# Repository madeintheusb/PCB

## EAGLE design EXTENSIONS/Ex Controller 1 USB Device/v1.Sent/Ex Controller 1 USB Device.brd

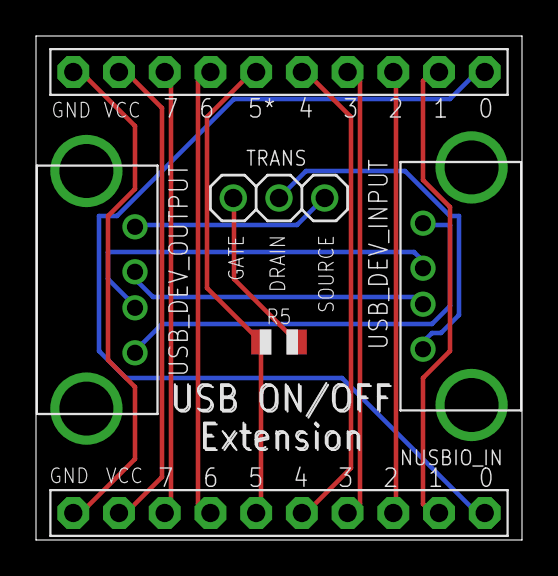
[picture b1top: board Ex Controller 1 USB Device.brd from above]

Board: 2 copper layers, 27.0 x 28.0 mm, 6 parts (0 on the bottom side), 16 nets.

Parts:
NUSBIO_IN: PINHD-1X10; 1X10-BIG
NUSBIO_OUT: PINHD-1X10; 1X10-BIG
R5: R0805
TRANS: 1X03
USB_DEV_INPUT: USB; USB-FEMALE-A-PTH
USB_DEV_OUTPUT: USB; USB-FEMALE-A-PTH

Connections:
GND: NUSBIO_IN.10, NUSBIO_OUT.10
GPIO0: NUSBIO_IN.1, NUSBIO_OUT.1
GPIO1: NUSBIO_IN.2, NUSBIO_OUT.2
GPIO2: NUSBIO_IN.3, NUSBIO_OUT.3
GPIO3: NUSBIO_IN.4, NUSBIO_OUT.4
GPIO4: NUSBIO_IN.5, NUSBIO_OUT.5
GPIO5: NUSBIO_IN.6, NUSBIO_OUT.6, R5.1
GPIO6: NUSBIO_IN.7, NUSBIO_OUT.7
GPIO7: NUSBIO_IN.8, NUSBIO_OUT.8
T_GATE: R5.2, TRANS.1
USB_DMINUS: USB_DEV_INPUT.D-, USB_DEV_OUTPUT.D-
USB_DPLUS: USB_DEV_INPUT.D+, USB_DEV_OUTPUT.D+
USB_GND: USB_DEV_INPUT.GND, USB_DEV_OUTPUT.GND
USB_VCC_IN: TRANS.2, USB_DEV_INPUT.VBUS
USB_VCC_OUT: TRANS.3, USB_DEV_OUTPUT.VBUS
VCC: NUSBIO_IN.9, NUSBIO_OUT.9

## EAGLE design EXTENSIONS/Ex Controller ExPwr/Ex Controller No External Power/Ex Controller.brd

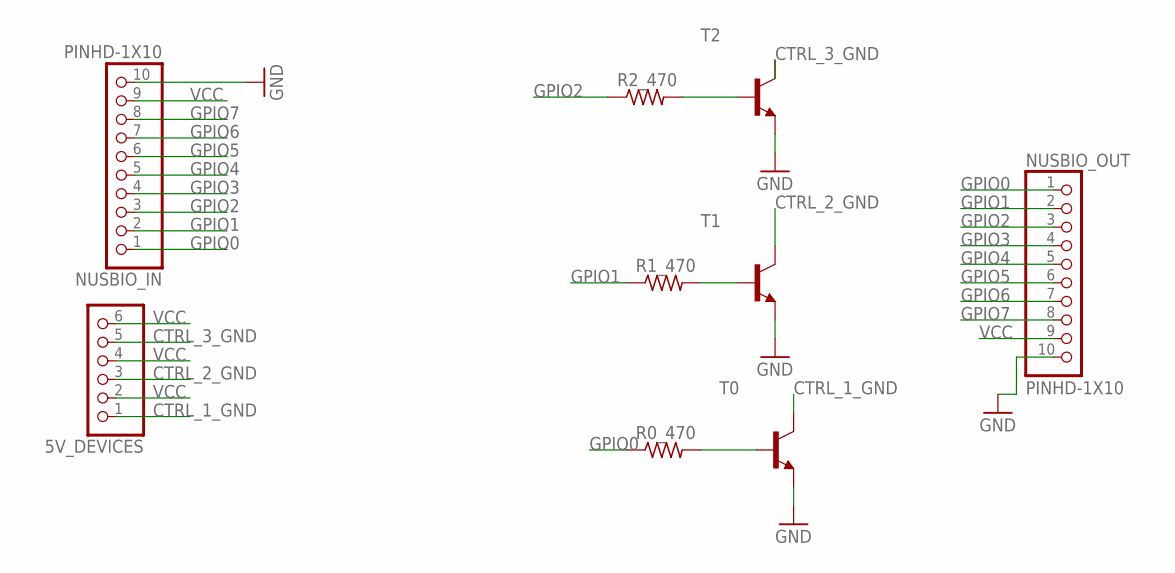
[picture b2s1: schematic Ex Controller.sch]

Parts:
5V_DEVICES: PINHD-1X6; 1X06
NUSBIO_IN: PINHD-1X10; 1X10-BIG
NUSBIO_OUT: PINHD-1X10; 1X10-BIG
R0_470, R1_470, R2_470: R-US_R0805; R0805
T0, T1, T2: MMBT3904LT1-NPN-SOT23-BEC; SOT23-BEC

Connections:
CTRL_1_GND: 5V_DEVICES.1, T0.C
CTRL_2_GND: 5V_DEVICES.3, T1.C
CTRL_3_GND: 5V_DEVICES.5, T2.C
GND: NUSBIO_IN.10, NUSBIO_OUT.10, T0.E, T1.E, T2.E
GPIO0: NUSBIO_IN.1, NUSBIO_OUT.1, R0_470.1
GPIO1: NUSBIO_IN.2, NUSBIO_OUT.2, R1_470.1
GPIO2: NUSBIO_IN.3, NUSBIO_OUT.3, R2_470.1
GPIO3: NUSBIO_IN.4, NUSBIO_OUT.4
GPIO4: NUSBIO_IN.5, NUSBIO_OUT.5
GPIO5: NUSBIO_IN.6, NUSBIO_OUT.6
GPIO6: NUSBIO_IN.7, NUSBIO_OUT.7
GPIO7: NUSBIO_IN.8, NUSBIO_OUT.8
unnamed: R2_470.2, T2.B
unnamed: R1_470.2, T1.B
unnamed: R0_470.2, T0.B
VCC: 5V_DEVICES.2, 5V_DEVICES.4, 5V_DEVICES.6, NUSBIO_IN.9, NUSBIO_OUT.9

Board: 2 copper layers, 9 parts (0 on the bottom side), 16 nets, no tracks yet.

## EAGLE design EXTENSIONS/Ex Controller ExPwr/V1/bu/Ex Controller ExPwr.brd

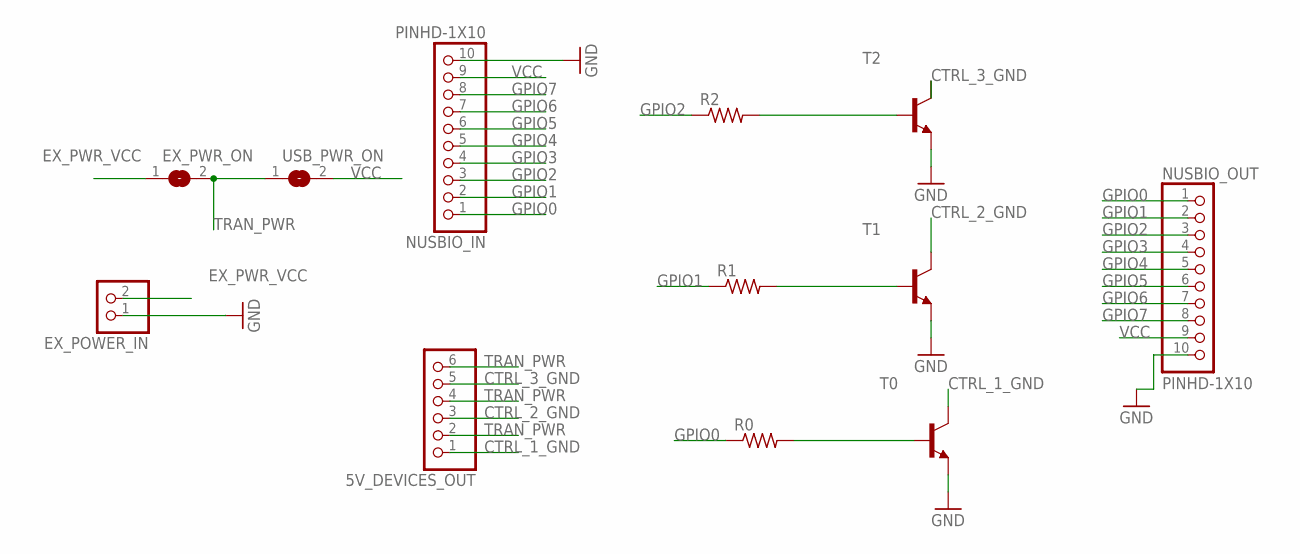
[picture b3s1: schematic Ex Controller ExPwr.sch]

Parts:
5V_DEVICES_OUT: PINHD-1X6; 1X06
EX_POWER_IN: PINHD-1X2; 1X02
EX_PWR_ON: SOLDERJUMPERREFLOW; SOLDERJUMPER_REFLOW
NUSBIO_IN: PINHD-1X10; 1X10-BIG
NUSBIO_OUT: PINHD-1X10; 1X10-BIG
R0, R1, R2: R-US_R0805; R0805
T0, T1, T2: MMBT3904LT1-NPN-SOT23-BEC; SOT23-BEC
USB_PWR_ON: SOLDERJUMPERREFLOW; SOLDERJUMPER_REFLOW

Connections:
CTRL_1_GND: 5V_DEVICES_OUT.1, T0.C
CTRL_2_GND: 5V_DEVICES_OUT.3, T1.C
CTRL_3_GND: 5V_DEVICES_OUT.5, T2.C
EX_PWR_VCC: EX_POWER_IN.2, EX_PWR_ON.1
GND: EX_POWER_IN.1, NUSBIO_IN.10, NUSBIO_OUT.10, T0.E, T1.E, T2.E
GPIO0: NUSBIO_IN.1, NUSBIO_OUT.1, R0.1
GPIO1: NUSBIO_IN.2, NUSBIO_OUT.2, R1.1
GPIO2: NUSBIO_IN.3, NUSBIO_OUT.3, R2.1
GPIO3: NUSBIO_IN.4, NUSBIO_OUT.4
GPIO4: NUSBIO_IN.5, NUSBIO_OUT.5
GPIO5: NUSBIO_IN.6, NUSBIO_OUT.6
GPIO6: NUSBIO_IN.7, NUSBIO_OUT.7
GPIO7: NUSBIO_IN.8, NUSBIO_OUT.8
unnamed: R2.2, T2.B
unnamed: R0.2, T0.B
unnamed: R1.2, T1.B
TRAN_PWR: 5V_DEVICES_OUT.2, 5V_DEVICES_OUT.4, 5V_DEVICES_OUT.6, EX_PWR_ON.2, USB_PWR_ON.1
VCC: NUSBIO_IN.9, NUSBIO_OUT.9, USB_PWR_ON.2

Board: 2 copper layers, 12 parts (0 on the bottom side), 18 nets, no tracks yet.

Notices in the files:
parts and their libraries:
microbuilder: This work is placed in the public domain, and may be freely used for commercial and non-commercial work with the following conditions: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
